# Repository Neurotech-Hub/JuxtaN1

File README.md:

# JuxtaN1

Matt Gaidica, Ph.D. | mgaidica@umich.edu

**Summary**

“Juxta” loggers are capable of detecting other nearby Juxta devices (~5 feet) using Bluetooth Low Energy (BLE). N-versions are meant to be implanted to record neural or cardiac biopotentials. They accomplish this by using a Universally Unique Identifier (UUID) that is unique to between Juxta loggers and other BLE devices, as well as a BLE address (or MAC address) unique to each physical BLE chip itself: All Juxta loggers emit the same UUID and each Juxta logger has a unique BLE address. When advertising, Juxta loggers will display as “J” followed by its unique BLE address (e.g., “J6CB2FDCDABB8”).
 
**Notes on terminology:**

* “Log Data/Logs” refer to data including the MAC address of another Juxta device. Typically, logs are made when the device is set to “Interval” mode and the device wakes up regularly to advertise and scan for other devices
* “Meta data” refers to any other type of data
Battery voltage and temperature are samples at regular intervals. When motion and magnet threshold is met, they are logged (sampling rate can be modified in Advanced Options)
* Logs and Meta Data are stored separately in memory and are functionally separable through user settings since a user may rely on one data type more than another.

---

Neuroscience 2023 Abstract
### Implantables to Correlate Social Interactions and Brain States in Free-living Animals

Wireless tracking devices have become indispensable tools in the analysis of free-living animal social networks. However, these devices, which rely on event-based data, do not provide insights into the accompanying temporal neural activity that occurs before, during, and after social interactions. To address this, we have transformed our wearable contact tracing technology into an implantable that can record neural or cardiac biopotentials, paving the way for richer animal behavior studies. We present this innovative form factor as one of the first to blend these technologies, developed using flexible circuit board substrates and biocompatible 3D printing. The result is a hormetically robust device applicable to a wide range of species. The device's functionality is complemented by a custom mobile application that allows users to configure device settings, establish recording schedules, and remotely upgrade the firmware as needed. We anticipate that this integrated platform will mark a significant step forward in the field of neuroethology, offering the potential for an enhanced understanding of animal behavior or broadening the scope of laboratory experiments.

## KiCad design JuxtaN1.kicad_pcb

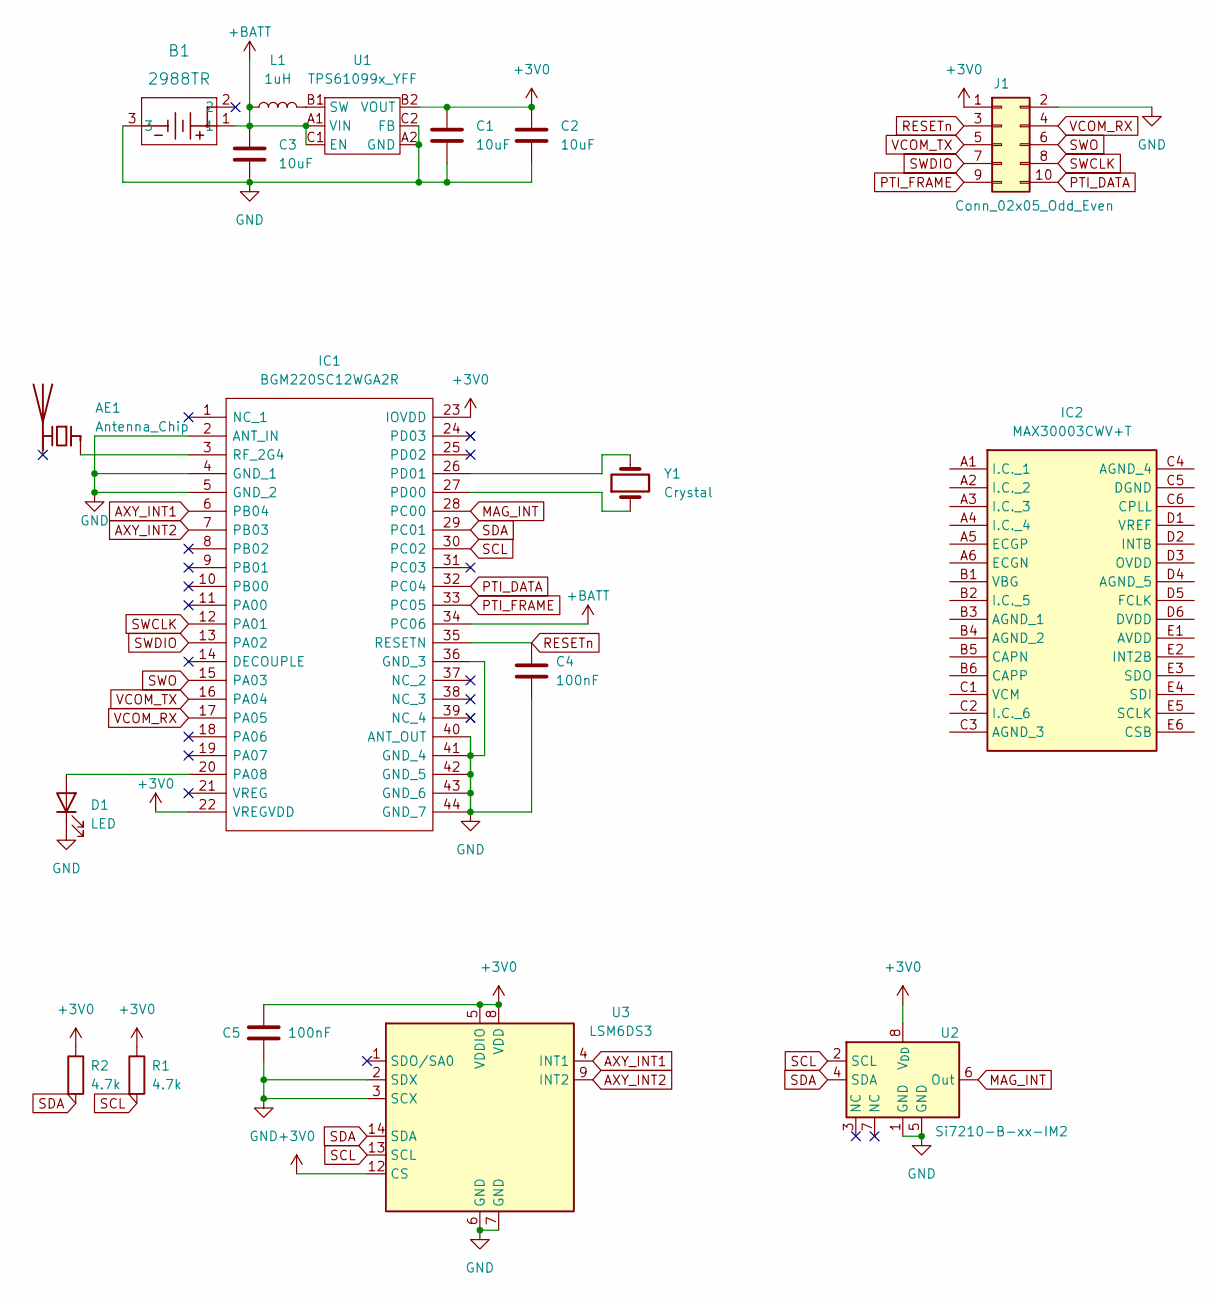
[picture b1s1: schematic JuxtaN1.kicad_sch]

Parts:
AE1: Antenna_Chip; 2450AT18B100; Mouser Part Number 609-2450AT18B100E; DigiKey 712-1006-1-ND
B1: 2988TR; 2988TR_KEY; Mouser Part Number 534-2988TR
C1, C2, C3: 10uF; C_0603_1608Metric; JLC C15525
C4, C5: 100nF; C_0402_1005Metric; JLC C1525
D1: LED; LED_0603_1608Metric; Mouser Part Number 755-SMLD12EN1WT86
IC1: BGM220SC12WGA2R; Mouser Part Number 634-BGM220SC12WGA2R
IC2: MAX30003CWV+T; BGA30C50P6X5_293X274X69; Mouser Part Number 700-MAX30003CWV+T
J1: Conn_02x05_Odd_Even; TC2050-IDC-FP
L1: 1uH; L_0805_2012Metric; Mouser Part Number 81-LQM21PN1R0MGHL
R1, R2: 4.7k; R_0402_1005Metric; JLC C105871
U1: TPS61099x_YFF; BGA-6_2x3_0.914x1.256mm; Mouser Part Number 595-TPS610993YFFR
U2: Si7210-B-xx-IM2; TDFN-8_1.4x1.6mm_P0.4mm; Mouser Part Number 634-SI7210-B-12-IM2
U3: LSM6DS3; LGA-14_3x2.5mm_P0.5mm_LayoutBorder3x4y; Mouser Part Number 511-LSM6DSOTR
Y1: Crystal; Crystal_SMD_2012-2Pin_2.0x1.2mm; JLC C127491

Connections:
+3V0: C1.1, C2.1, C5.1, IC1.22 (VREGVDD), IC1.23 (IOVDD), J1.1, R1.1, R2.1, U1.B2 (VOUT), U2.8 (V_{DD}), U3.5 (VDDIO), U3.8 (VDD), U3.12 (CS)
+BATT: B1.1, C3.1, IC1.34 (PC06), L1.1, U1.A1 (VIN), U1.C1 (EN)
AXY_INT1: IC1.6 (PB04), U3.4 (INT1)
AXY_INT2: IC1.7 (PB03), U3.9 (INT2)
GND: B1.3, C1.2, C2.2, C3.2, C4.2, C5.2, D1.1 (K), IC1.2 (ANT_IN), IC1.4 (GND_1), IC1.5 (GND_2), IC1.36 (GND_3), IC1.40 (ANT_OUT), IC1.41 (GND_4), IC1.42 (GND_5), IC1.43 (GND_6), IC1.44 (GND_7), J1.2, U1.A2 (GND), U1.C2 (FB), U2.1 (GND), U2.5 (GND), U3.2 (SDX), U3.3 (SCX), U3.6 (GND), U3.7 (GND)
MAG_INT: IC1.28 (PC00), U2.6 (Out)
unnamed: AE1.1 (FEED), IC1.3 (RF_2G4)
unnamed: D1.2 (A), IC1.20 (PA08)
unnamed: IC1.27 (PD00), Y1.1
unnamed: IC1.26 (PD01), Y1.2
unnamed: L1.2, U1.B1 (SW)
PTI_DATA: IC1.32 (PC04), J1.10
PTI_FRAME: IC1.33 (PC05), J1.9
RESETn: C4.1, IC1.35 (RESETN), J1.3
SCL: IC1.30 (PC02), R1.2, U2.2 (SCL), U3.13 (SCL)
SDA: IC1.29 (PC01), R2.2, U2.4 (SDA), U3.14 (SDA)
SWCLK: IC1.12 (PA01), J1.8
SWDIO: IC1.13 (PA02), J1.7
SWO: IC1.15 (PA03), J1.6
VCOM_RX: IC1.17 (PA05), J1.4
VCOM_TX: IC1.16 (PA04), J1.5

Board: 2 copper layers, 18 parts (0 on the bottom side), 21 nets, no tracks yet.

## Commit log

2023-06-10 Init
2023-06-12 ignore
2023-06-13 Readme
2023-06-21 Considering other AFEs
